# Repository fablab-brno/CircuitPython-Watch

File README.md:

# CircuitPython Watch

This is sort of CircuitPlayground Express clone with Neopixel ring and RTC DS3231.

Goal of this board is make real working watch for Maker Faire Prague (MFP) which can children age of 10+ years make at workshop and which can after that use to learn Circuitpython.   

Sadly we encountered some issues at MFP with assembly of the board, so just 2 watches were made. 

Until now, there were 2 revisions of the board: 

version A: 
- I2C was routed to wrong pins
- VCC was split in 2 signals in schematic so I have to connect them at board with wire
- VBAT was connected to 5V so if I tryed to charge battery there was to much voltage and battery did not charge
- it has not SWDIO & SWCLK pins so I had to solder wires to the pins of the CPU to burn the bootloader
	
version B:
- board is working & ready for MFP
	
Description of the board:
- uses ATSAMD21G18 like CPX
- uses AP131 voltage regulator (5V -> 3.3V)
- uses MCP73831 for battery charging
- uses DS3231 for RTC
- uses UF2 bootloader
- uses micro USB connector for charging & data transfer
- uses 12 WS2812B RGB diodes to schow time
	
Description of usage:

There are 2 touch buttons on the board. 

Button A is "Time button", when is pressed, it will show hours by blue color on RGB LEDs and minutes by green color. Every minute is schowed by 1 blink of green color. 

Button B is  "Mode button", when is pressed, it will increase counter by 1 and it will schow predefined animation from main.py .

Function is showed in gif bellow, in loop with all default animations. 
<p>

</p>

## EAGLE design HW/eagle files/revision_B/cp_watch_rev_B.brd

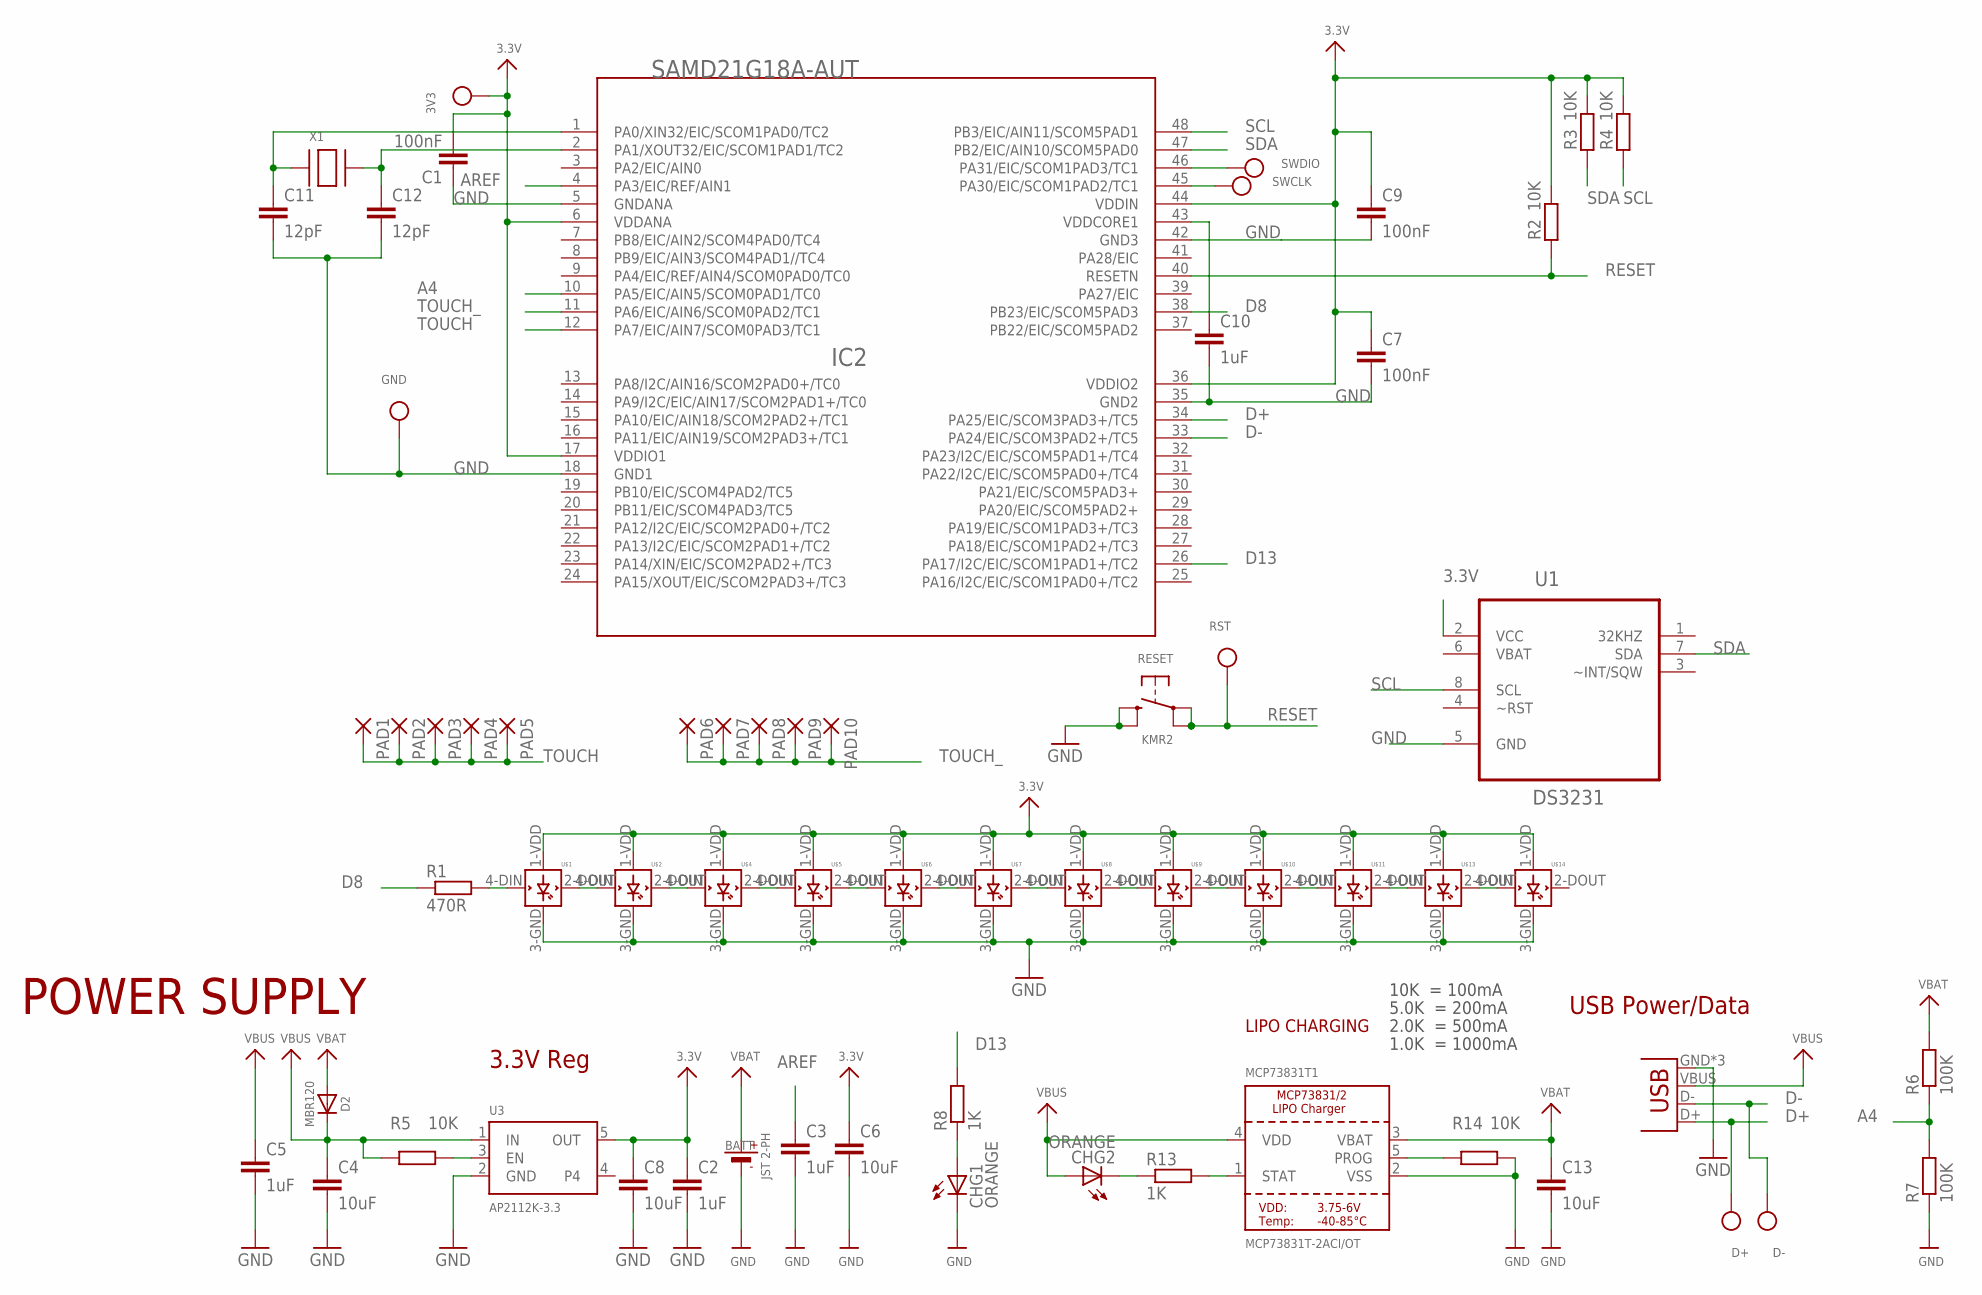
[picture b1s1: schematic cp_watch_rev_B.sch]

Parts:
3V3: TESTPOINTROUND1MM; TESTPOINT_ROUND_1MM
BATT: JST 2-PH; JSTPH2
C1, C7, C9: 100nF; C0805
C2, C3, C5, C10: 1uF; C0805
C4, C6, C8, C13: 10uF; C0805
C11, C12: 12pF; C0805
CHG1, CHG2: ORANGE; CHIPLED_0805
D2: MBR120; SOD-123
D+: TESTPOINTROUND1MM; TESTPOINT_ROUND_1MM
D-: TESTPOINTROUND1MM; TESTPOINT_ROUND_1MM
GND: TESTPOINTROUND1MM; TESTPOINT_ROUND_1MM
IC2: SAMD21G18A-AUT; TQFP48
MCP73831T1: MCP73831T-2ACI/OT; SOT23-5
PAD1, PAD2, PAD3, PAD4, PAD5, PAD6, PAD7, PAD8, PAD9, PAD10: SMD5; SMD2,54-5,08
R1: 470R; R0805
R2, R3, R4, R5, R14: 10K; R0805
R6, R7: 100K; R0805
R8, R13: 1K; R0805
RESET: KMR2; BTN_KMR2_4.6X2.8
RST: TESTPOINTROUND1MM; TESTPOINT_ROUND_1MM
SWCLK: TESTPOINTROUND1MM; TESTPOINT_ROUND_1MM
SWDIO: TESTPOINTROUND1MM; TESTPOINT_ROUND_1MM
U1: DS3231; SOIC8_150MIL
U3: AP2112K-3.3; SOT95P290X120-5
U$1, U$2, U$4, U$5, U$6, U$7, U$8, U$9, U$10, U$11, U$13, U$14: WS2812B
USB: USB_MICRO_ATTEND_; USB_MICRO
X1: XTALNX5032; NX5032

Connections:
3.3V: 3V3.P$1, C1.2, C2.1, C6.1, C7.1, C8.1, C9.1, IC2.6 (VDDANA), IC2.17 (VDDIO1), IC2.36 (VDDIO2), IC2.44 (VDDIN), R2.2, R3.2, R4.2, U1.2 (VCC), U3.5 (OUT), U$1.1-VDD (VDD), U$2.1-VDD (VDD), U$4.1-VDD (VDD), U$5.1-VDD (VDD), U$6.1-VDD (VDD), U$7.1-VDD (VDD), U$8.1-VDD (VDD), U$9.1-VDD (VDD), U$10.1-VDD (VDD), U$11.1-VDD (VDD), U$13.1-VDD (VDD), U$14.1-VDD (VDD)
A4: IC2.10 (PA5/EIC/AIN5/SCOM0PAD1/TC0), R6.1, R7.2
AREF: C3.1, IC2.4 (PA3/EIC/REF/AIN1)
D8: IC2.38 (PB23/EIC/SCOM5PAD3), R1.1
D13: IC2.26 (PA17/I2C/EIC/SCOM1PAD1+/TC2), R8.2
D+: D+.P$1, IC2.34 (PA25/EIC/SCOM3PAD3+/TC5), USB.D+
D-: D-.P$1, IC2.33 (PA24/EIC/SCOM3PAD2+/TC5), USB.D-
GND: BATT.1 (-), C1.1, C2.2, C3.2, C4.2, C5.2, C6.2, C7.2, C8.2, C9.2, C10.2, C11.2, C12.2, C13.2, CHG1.C, GND.P$1, IC2.5 (GNDANA), IC2.18 (GND1), IC2.35 (GND2), IC2.42 (GND3), MCP73831T1.2 (VSS), R7.1, R14.2, RESET.B (S), RESET.B' (S1), U1.5 (GND), U3.2 (GND), U$1.3-GND (GND), U$2.3-GND (GND), U$4.3-GND (GND), U$5.3-GND (GND), U$6.3-GND (GND), U$7.3-GND (GND), U$8.3-GND (GND), U$9.3-GND (GND), U$10.3-GND (GND), U$11.3-GND (GND), U$13.3-GND (GND), U$14.3-GND (GND), USB.GND, USB.GND@2 (GND), USB.GND@3 (GND)
unnamed: C11.1, IC2.1 (PA0/XIN32/EIC/SCOM1PAD0/TC2), X1.P$1
unnamed: IC2.45 (PA30/EIC/SCOM1PAD2/TC1), SWCLK.P$1
unnamed: R5.2, U3.3 (EN)
unnamed: R1.2, U$1.4-DIN (DIN)
unnamed: C10.1, IC2.43 (VDDCORE1)
unnamed: U$1.2-DOUT (DOUT), U$2.4-DIN (DIN)
unnamed: C12.1, IC2.2 (PA1/XOUT32/EIC/SCOM1PAD1/TC2), X1.P$2
unnamed: U$2.2-DOUT (DOUT), U$4.4-DIN (DIN)
unnamed: U$4.2-DOUT (DOUT), U$5.4-DIN (DIN)
unnamed: U$5.2-DOUT (DOUT), U$6.4-DIN (DIN)
unnamed: U$6.2-DOUT (DOUT), U$7.4-DIN (DIN)
unnamed: U$7.2-DOUT (DOUT), U$8.4-DIN (DIN)
unnamed: U$8.2-DOUT (DOUT), U$9.4-DIN (DIN)
unnamed: U$9.2-DOUT (DOUT), U$10.4-DIN (DIN)
unnamed: U$10.2-DOUT (DOUT), U$11.4-DIN (DIN)
unnamed: U$11.2-DOUT (DOUT), U$13.4-DIN (DIN)
unnamed: U$13.2-DOUT (DOUT), U$14.4-DIN (DIN)
unnamed: CHG1.A, R8.1
unnamed: CHG2.C, R13.1
unnamed: MCP73831T1.1 (STAT), R13.2
unnamed: MCP73831T1.5 (PROG), R14.1
RESET: IC2.40 (RESETN), R2.1, RESET.A, RESET.A' (P1), RST.P$1
SCL: IC2.48 (PB3/EIC/AIN11/SCOM5PAD1), R4.1, U1.8 (SCL)
SDA: IC2.47 (PB2/EIC/AIN10/SCOM5PAD0), R3.1, U1.7 (SDA)
SWDIO: IC2.46 (PA31/EIC/SCOM1PAD3/TC1), SWDIO.P$1
TOUCH: IC2.12 (PA7/EIC/AIN7/SCOM0PAD3/TC1), PAD1.1, PAD2.1, PAD3.1, PAD4.1, PAD5.1
TOUCH_: IC2.11 (PA6/EIC/AIN6/SCOM0PAD2/TC1), PAD6.1, PAD7.1, PAD8.1, PAD9.1, PAD10.1
VBAT: BATT.2 (+), C13.1, D2.A, MCP73831T1.3 (VBAT), R6.2, U1.6 (VBAT)
VBUS: C4.1, C5.1, CHG2.A, D2.C, MCP73831T1.4 (VDD), R5.1, U3.1 (IN), USB.VBUS

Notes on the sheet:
USB Power/Data
3.3V Reg
POWER SUPPLY
10K = 100mA
5.0K = 200mA
2.0K = 500mA
1.0K = 1000mA
LIPO CHARGING

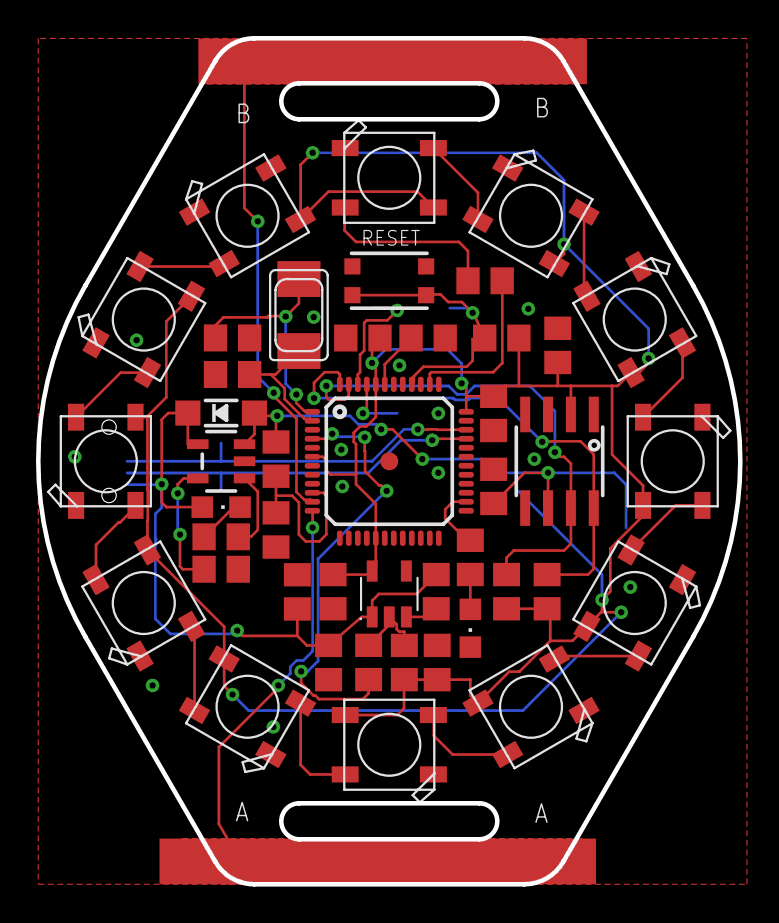
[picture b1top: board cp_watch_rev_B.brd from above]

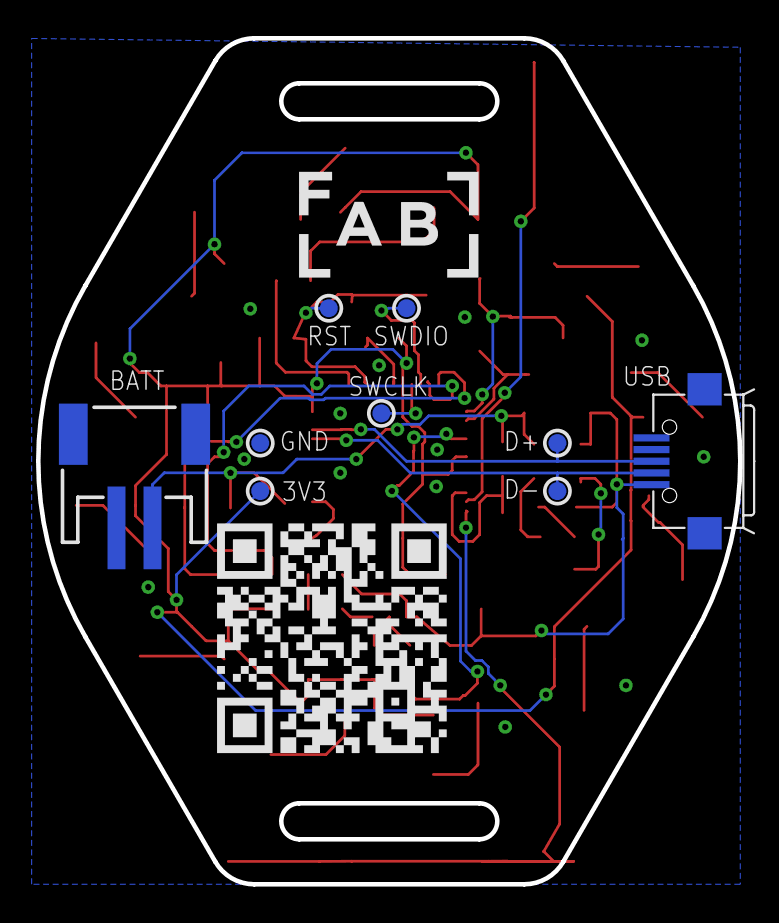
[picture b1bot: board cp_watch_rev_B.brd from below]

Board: 2 copper layers, 39.0 x 47.0 mm, 63 parts (9 on the bottom side), 37 nets.

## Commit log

2018-06-28 Change in README
2018-07-15 files upload
2018-08-02 images upload

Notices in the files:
parts and their libraries:
microbuilder: This work is placed in the public domain, and may be freely used for commercial and non-commercial work with the following conditions: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
